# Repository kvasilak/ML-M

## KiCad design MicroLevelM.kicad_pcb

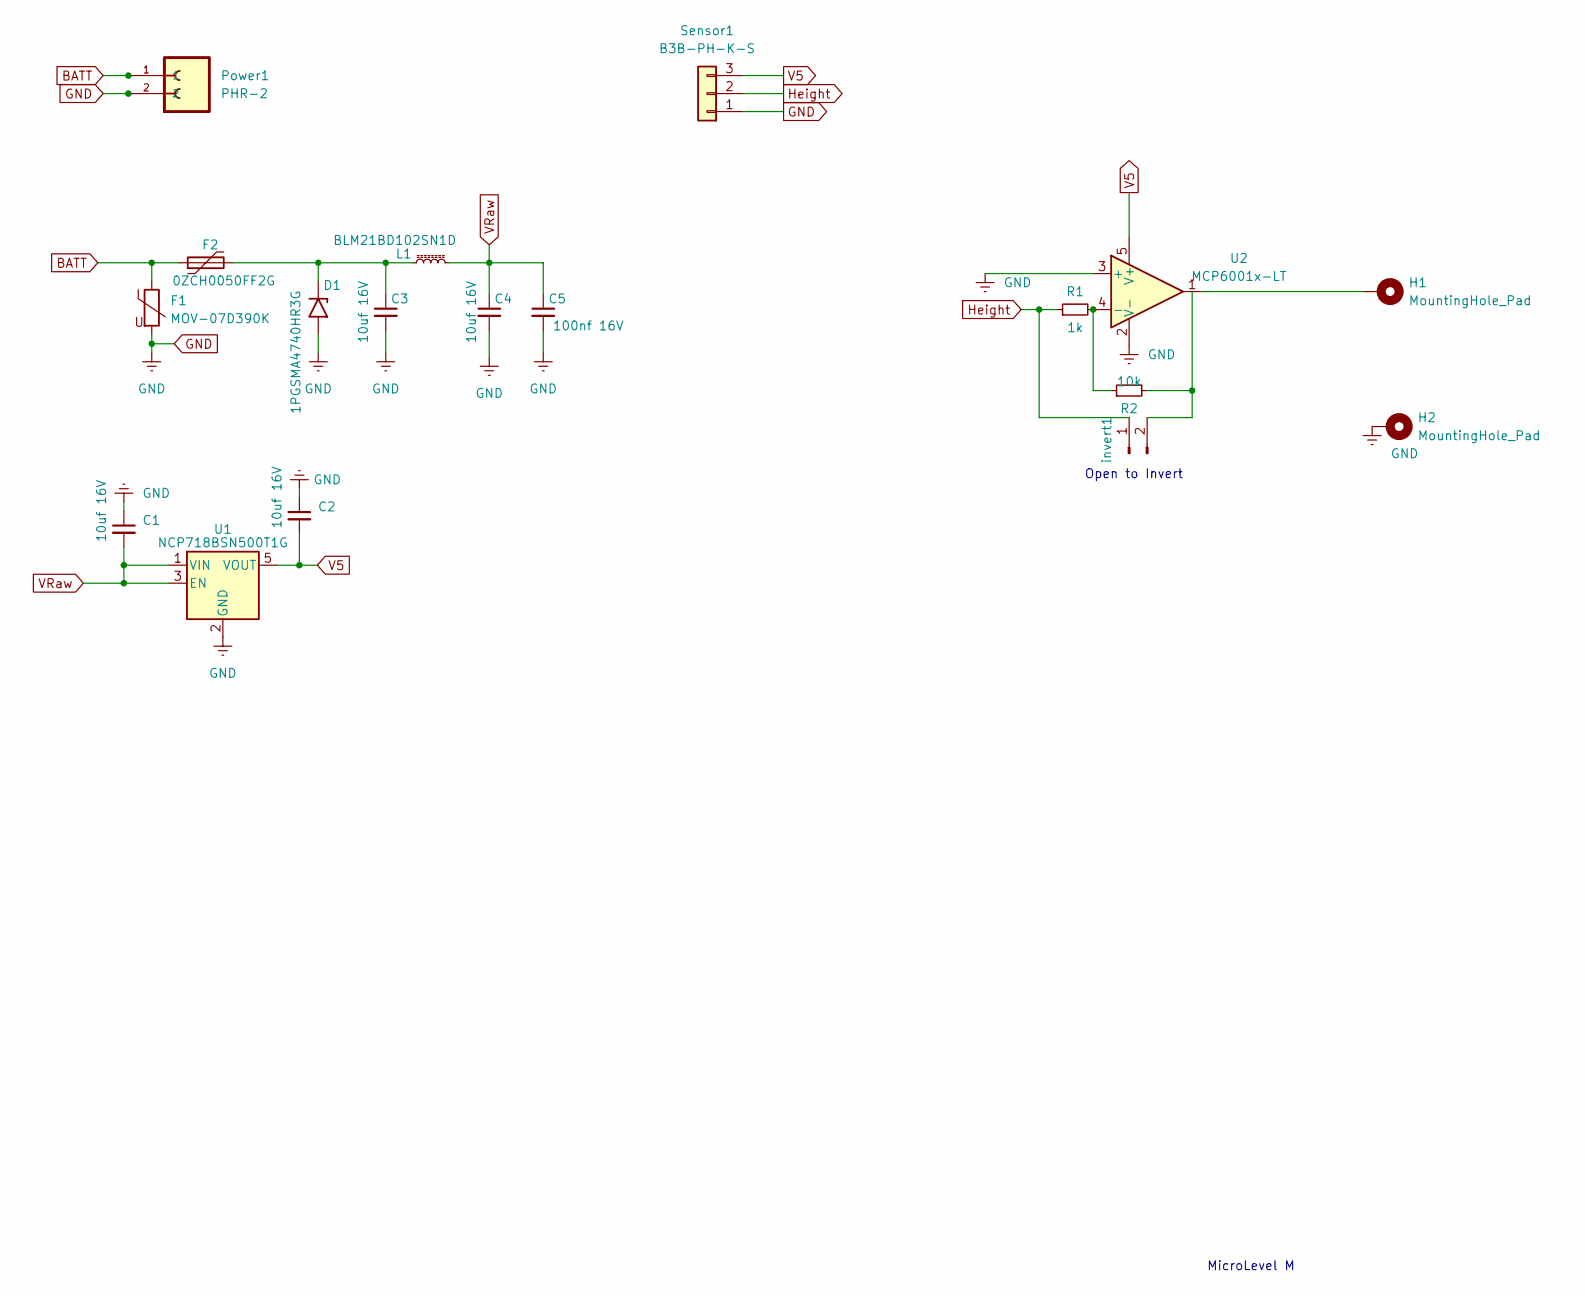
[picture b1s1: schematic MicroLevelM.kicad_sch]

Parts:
C1, C2, C3, C4: 10uf 16V; C_0805_2012Metric_Pad1.18x1.45mm_HandSolder
C5: 100nf 16V; C_0805_2012Metric_Pad1.18x1.45mm_HandSolder
D1: 1PGSMA4740HR3G; D_SMB
F1: MOV-07D390K; RV_Disc_D7mm_W3.4mm_P5mm
F2: 0ZCH0050FF2G; Fuse_1206_3216Metric_Pad1.42x1.75mm_HandSolder
H1, H2: MountingHole_Pad; MountingHole_4mm_Pad
L1: BLM21BD102SN1D; L_0805_2012Metric
Power1: PHR-2; JST_PHR-2
R1: 1k; R_0805_2012Metric
R2: 10k; R_0805_2012Metric
Sensor1: B3B-PH-K-S; JST_PH_B3B-PH-K_1x03_P2.00mm_Vertical
U1: NCP718BSN500T1G; SOT-23-5
U2: MCP6001x-LT; SOT-353_SC-70-5
invert1: Header_01x02_Male; PinHeader_1x02_P2.54mm_Vertical

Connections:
BATT: F1.1, F2.1, Power1.1
GND: C1.1, C2.1, C3.2, C4.2, C5.2, D1.2 (A2), F1.2, H2.1, Power1.2, Sensor1.1, U1.2 (GND), U2.2 (V-), U2.3 (+)
Height: R1.1, Sensor1.2, invert1.1
unnamed: C3.1, D1.1 (A1), F2.2, L1.1
unnamed: R1.2, R2.1, U2.4 (-)
unnamed: H1.1, U2.1
unnamed: R2.2, invert1.2
V5: C2.2, Sensor1.3, U1.5 (VOUT), U2.5 (V+)
VRaw: C1.2, C4.1, C5.1, L1.2, U1.1 (VIN), U1.3 (EN)

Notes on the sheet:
Open to Invert
MicroLevel M

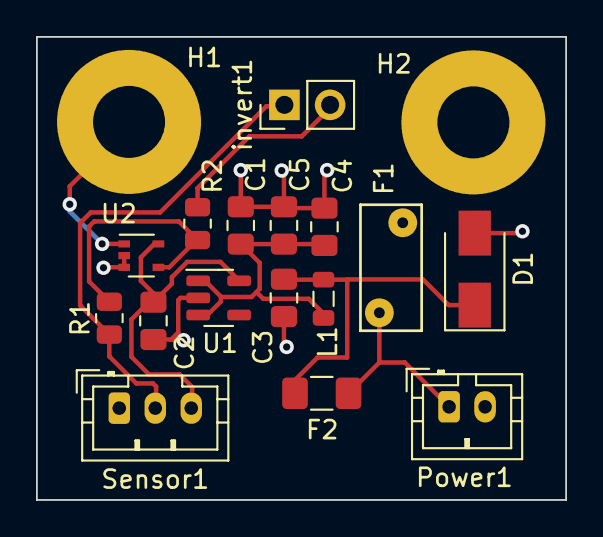
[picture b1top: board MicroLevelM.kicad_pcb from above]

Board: 2 copper layers, 29.4 x 25.7 mm, 18 parts (0 on the bottom side), 9 nets.
